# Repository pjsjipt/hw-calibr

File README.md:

# hw-calibr
Anemometer calibration system using mass flow meters

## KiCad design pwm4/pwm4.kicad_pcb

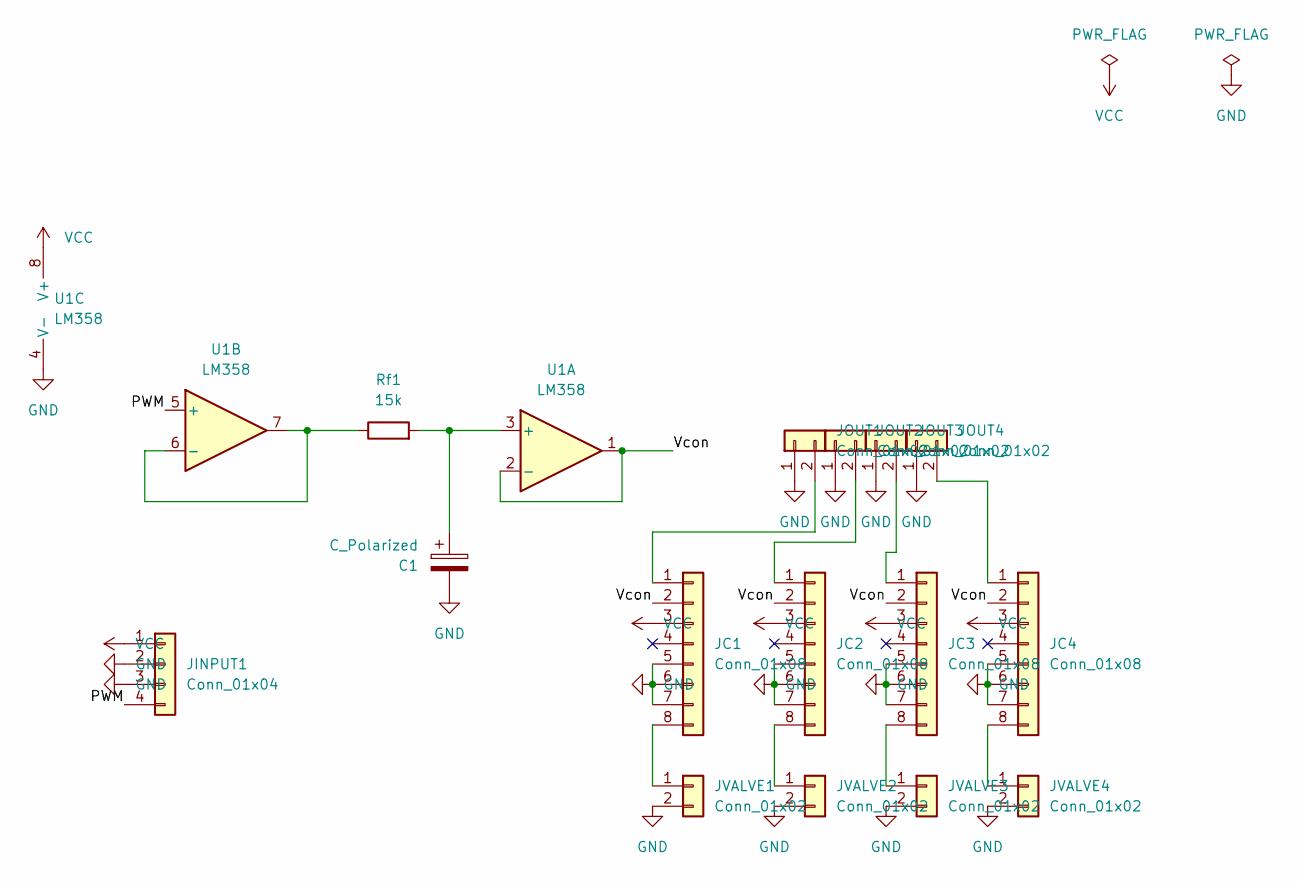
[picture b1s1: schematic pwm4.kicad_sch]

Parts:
C1: C_Polarized; CP_Radial_D5.0mm_P2.50mm
JC1, JC2, JC3, JC4: Conn_01x08; PinHeader_1x08_P2.54mm_Vertical
JINPUT1: Conn_01x04; TerminalBlock_bornier-4_P5.08mm
JOUT1, JOUT2, JOUT3, JOUT4: Conn_01x02; TerminalBlock_bornier-2_P5.08mm
JVALVE1, JVALVE2, JVALVE3, JVALVE4: Conn_01x02; TerminalBlock_bornier-2_P5.08mm
Rf1: 15k; R_Axial_DIN0207_L6.3mm_D2.5mm_P10.16mm_Horizontal
U1: LM358; DIP-8_W7.62mm

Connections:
/PWM: JINPUT1.4, U1.5 (+)
/Vcon: JC1.2, JC2.2, JC3.2, JC4.2, U1.1, U1.2 (-)
GND: C1.2, JC1.5, JC1.6, JC1.7, JC2.5, JC2.6, JC2.7, JC3.5, JC3.6, JC3.7, JC4.5, JC4.6, JC4.7, JINPUT1.2, JINPUT1.3, JOUT1.1, JOUT2.1, JOUT3.1, JOUT4.1, JVALVE1.2, JVALVE2.2, JVALVE3.2, JVALVE4.2, U1.4 (V-)
unnamed: C1.1, Rf1.2, U1.3 (+)
unnamed: JC1.1, JOUT1.2
unnamed: JC1.8, JVALVE1.1
unnamed: JC2.1, JOUT2.2
unnamed: JC2.8, JVALVE2.1
unnamed: JC3.1, JOUT3.2
unnamed: JC3.8, JVALVE3.1
unnamed: JC4.1, JOUT4.2
unnamed: JC4.8, JVALVE4.1
unnamed: Rf1.1, U1.6 (-), U1.7
VCC: JC1.3, JC2.3, JC3.3, JC4.3, JINPUT1.1, U1.8 (V+)

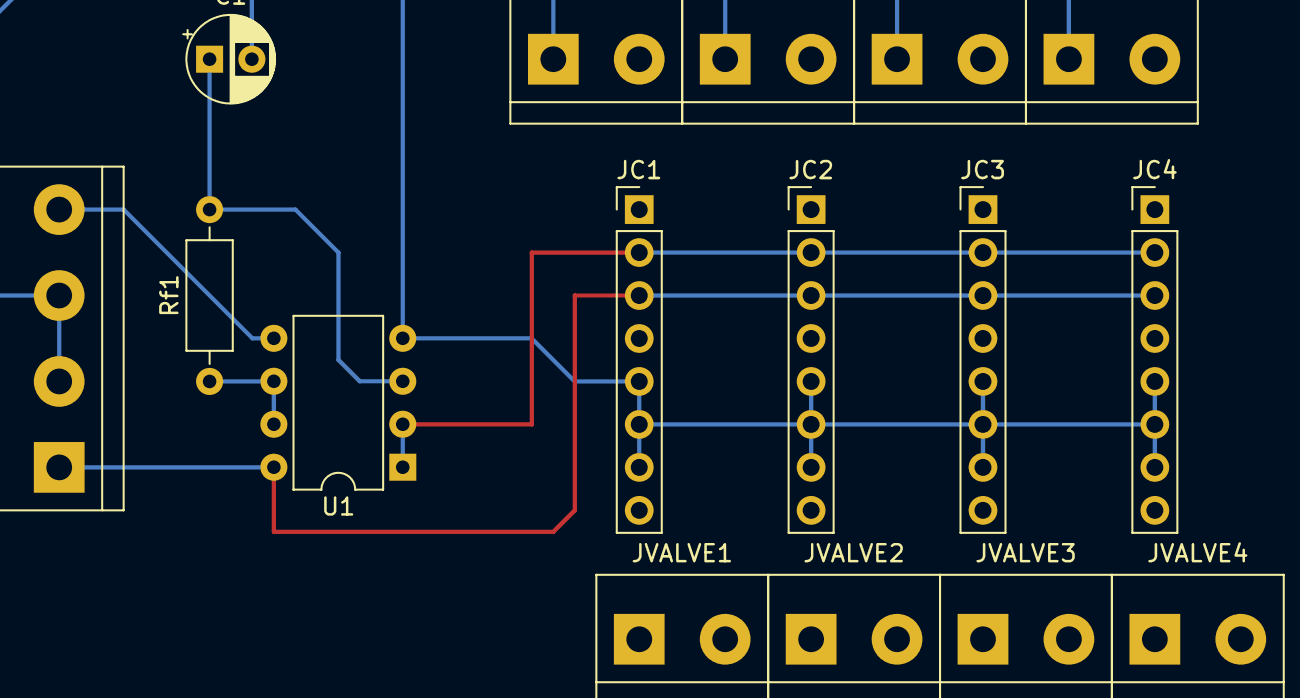
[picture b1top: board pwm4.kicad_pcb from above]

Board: 2 copper layers, 16 parts (0 on the bottom side), 14 nets.

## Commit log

2022-06-09 Initial commit of the anemometer calibration system.
    For now it has
    * Geometry of the mini wind tunnel for 3d printing
    * PCB board for mass flow controllers
    * Arduino software
